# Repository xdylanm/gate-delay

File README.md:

# Gate Delay

A gate delay module in the Eurorack format. The module is implemented with an ATTiny13a microcontroller, with features including

* delays ranging from about 8ms to 2s
* gate pulse length is maintined
* sequences of up to 4 pulses can be delayed

A second, fully analog design is also described. This design is based on a current mirror and integration capacitor, and also maintains the gate pulse length. I have not implemented and tested this one.

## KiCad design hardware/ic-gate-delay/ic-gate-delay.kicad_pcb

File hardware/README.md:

The 'dual-gate-delay' project contains the hardware design for the v1.0 module. The 'gate-delay' project only contains schematic sketches (for reference related to the analog variant of the design). The 'ic-gate-delay' project is the v2.0 module (single gate delay with expanded IO).

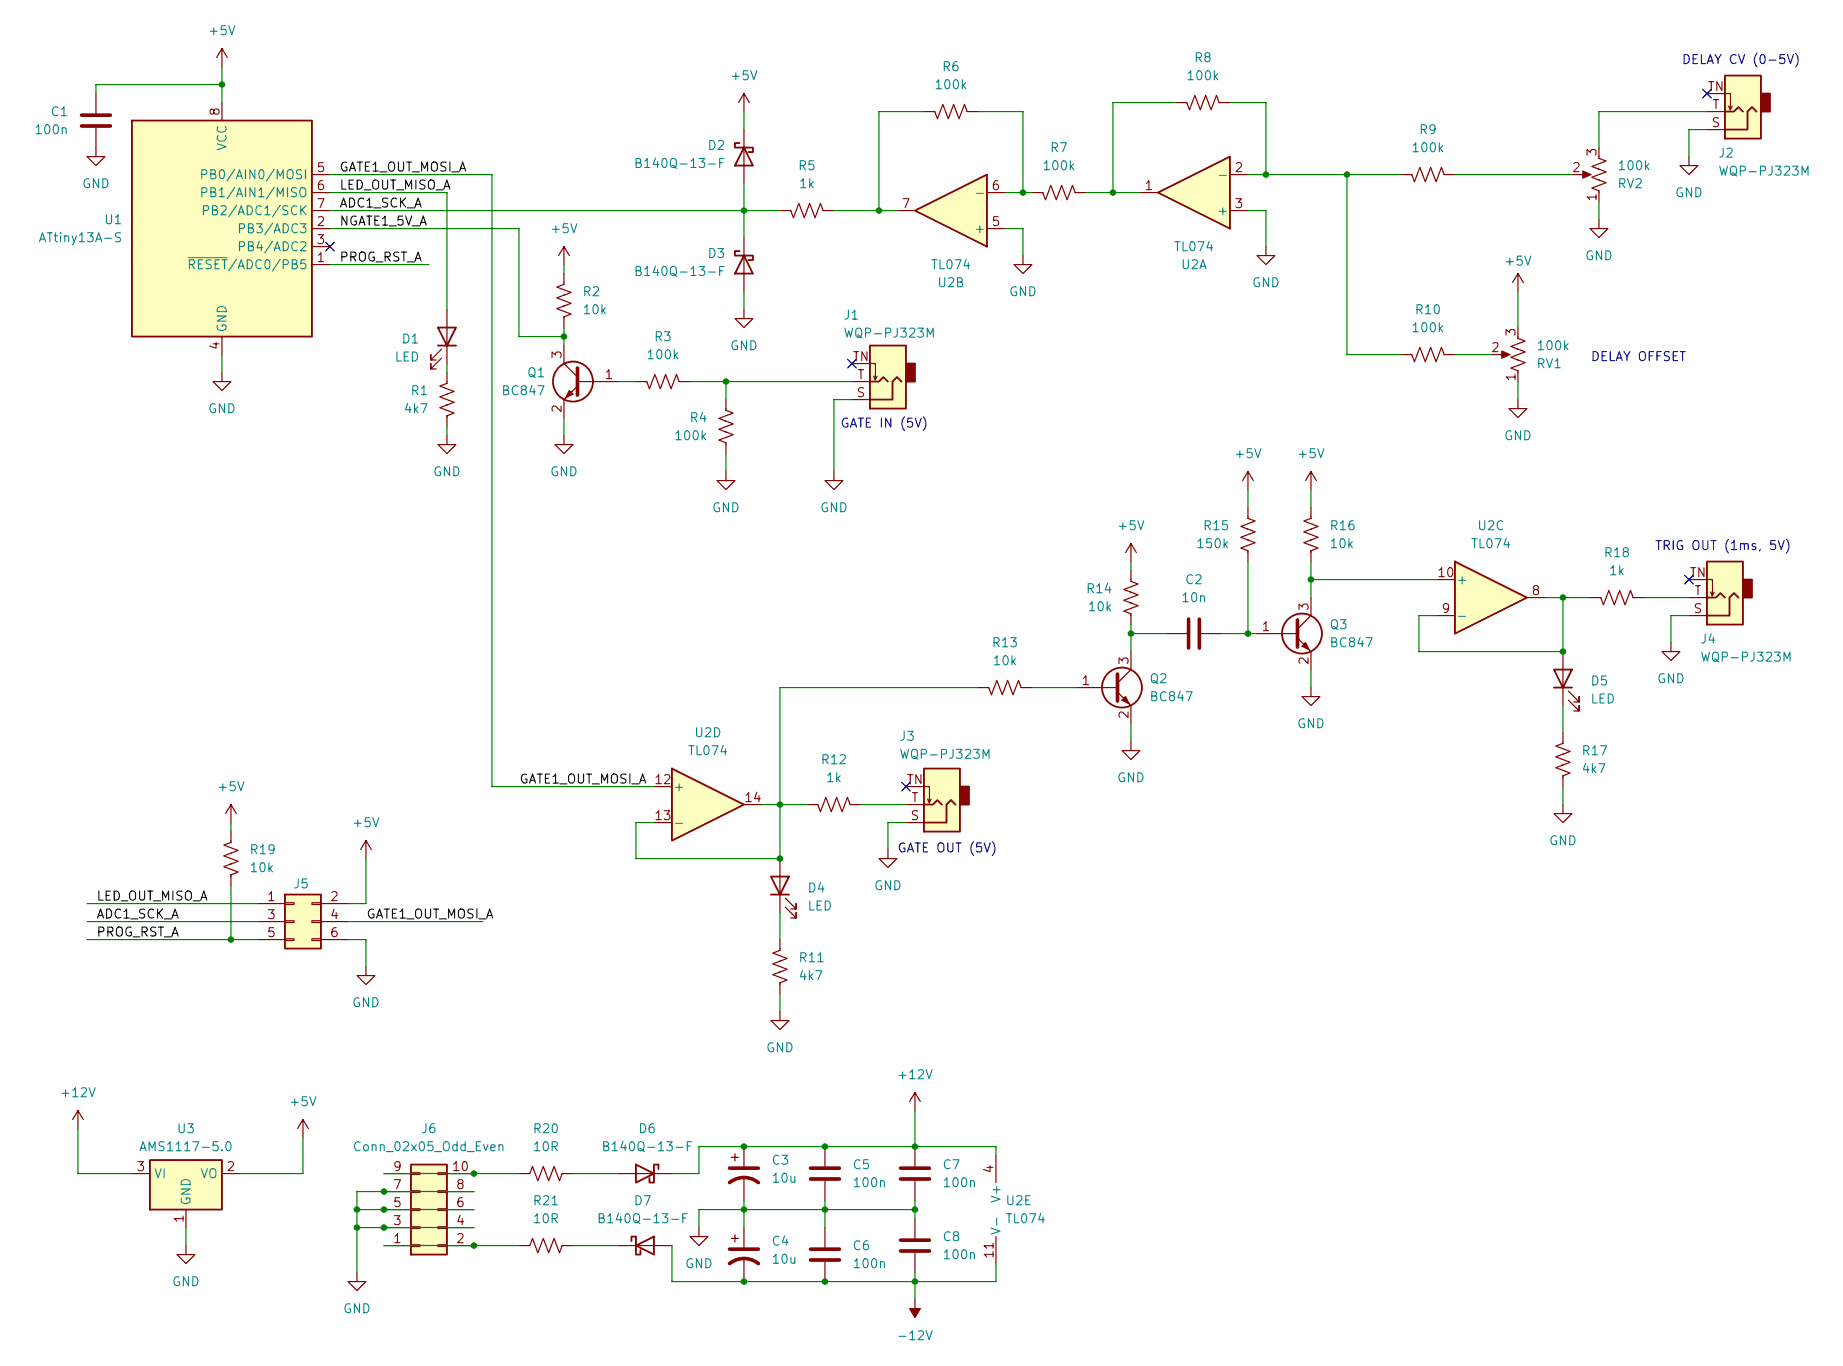
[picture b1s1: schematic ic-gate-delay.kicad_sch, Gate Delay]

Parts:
C1, C5, C6, C7, C8: 100n; C_0805_2012Metric
C2: 10n; C_0805_2012Metric
C3, C4: 10u; CP_Radial_D5.0mm_P2.50mm
D1: LED; LED_0805_2012Metric_Pad1.15x1.40mm_HandSolder
D2, D3, D6, D7: B140Q-13-F; D_SMA_Handsoldering
D4, D5: LED; LED_D3.0mm
J1, J2, J3, J4: WQP-PJ323M; Jack_3.5mm_QingPu_WQP-PJ323M_Horizontal
J5: Conn_02x03_Odd_Even; PinHeader_2x03_P2.54mm_Vertical
J6: Conn_02x05_Odd_Even; IDC-Header_2x05_P2.54mm_Horizontal
Q1, Q2, Q3: BC847; SOT-23
R1, R11, R17: 4k7; R_0805_2012Metric_Pad1.20x1.40mm_HandSolder
R2, R13, R14, R16, R19: 10k; R_0805_2012Metric_Pad1.20x1.40mm_HandSolder
R3, R4, R6, R7, R8, R9, R10: 100k; R_0805_2012Metric_Pad1.20x1.40mm_HandSolder
R5, R12, R18: 1k; R_0805_2012Metric_Pad1.20x1.40mm_HandSolder
R15: 150k; R_0805_2012Metric_Pad1.20x1.40mm_HandSolder
R20, R21: 10R; R_0805_2012Metric_Pad1.20x1.40mm_HandSolder
RV1, RV2: 100k; Potentiometer_Bourns_PTV09A-2_Single_Horizontal
U1: ATtiny13A-S; SOIC-8_3.9x4.9mm_P1.27mm
U2: TL074; SOIC-14_3.9x8.7mm_P1.27mm
U3: AMS1117-5.0; SOT-223-3_TabPin2

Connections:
+5V: C1.1, D2.1 (K), J5.2, R2.1, R14.1, R15.1, R16.1, R19.1, RV1.3, U1.8 (VCC), U3.2 (VO)
+12V: C3.1, C5.1, C7.1, D6.1 (K), U2.4 (V+), U3.3 (VI)
-12V: C4.2, C6.2, C8.2, D7.2 (A), U2.11 (V-)
/ADC1_SCK_A: D2.2 (A), D3.1 (K), J5.3, R5.1, U1.7 (PB2/ADC1/SCK)
/GATE1_OUT_MOSI_A: J5.4, U1.5 (PB0/AIN0/MOSI), U2.12 (+)
/LED_OUT_MISO_A: D1.2 (A), J5.1, U1.6 (PB1/AIN1/MISO)
/NGATE1_5V_A: Q1.3 (C), R2.2, U1.2 (PB3/ADC3)
/PROG_RST_A: J5.5, R19.2, U1.1 (~RESET/ADC0/PB5)
GND: C1.2, C3.2, C4.1, C5.2, C6.1, C7.2, C8.1, D3.2 (A), J1.S, J2.S, J3.S, J4.S, J5.6, J6.3, J6.4, J6.5, J6.6, J6.7, J6.8, Q1.2 (E), Q2.2 (E), Q3.2 (E), R1.2, R4.2, R11.2, R17.2, RV1.1, RV2.1, U1.4 (GND), U2.3 (+), U2.5 (+), U3.1 (GND)
unnamed: D1.1 (K), R1.1
unnamed: D4.2 (A), R12.2, R13.2, U2.13 (-), U2.14
unnamed: D4.1 (K), R11.1
unnamed: D5.2 (A), R18.2, U2.8, U2.9 (-)
unnamed: D5.1 (K), R17.1
unnamed: D6.2 (A), R20.2
unnamed: D7.1 (K), R21.2
unnamed: J1.T, R3.1, R4.1
unnamed: J2.T, RV2.3
unnamed: J3.T, R12.1
unnamed: J4.T, R18.1
unnamed: J6.1, J6.2, R21.1
unnamed: J6.9, J6.10, R20.1
unnamed: Q1.1 (B), R3.2
unnamed: Q2.1 (B), R13.1
unnamed: C2.1, Q2.3 (C), R14.2
unnamed: C2.2, Q3.1 (B), R15.2
unnamed: Q3.3 (C), R16.2, U2.10 (+)
unnamed: R5.2, R6.1, U2.7
unnamed: R7.2, R8.1, U2.1
unnamed: R9.2, RV2.2
unnamed: R10.2, RV1.2
unnamed: R8.2, R9.1, R10.1, U2.2 (-)
unnamed: R6.2, R7.1, U2.6 (-)

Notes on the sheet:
DELAY OFFSET
GATE IN (5V)
TRIG OUT (1ms, 5V)
GATE OUT (5V)
DELAY CV (0-5V)

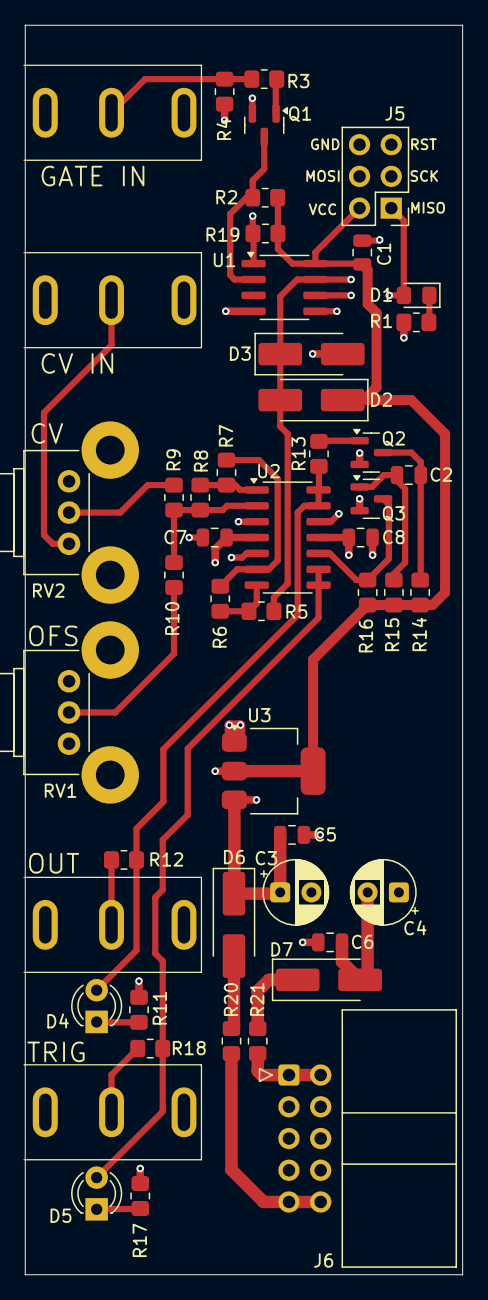
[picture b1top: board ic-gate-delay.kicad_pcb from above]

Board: 4 copper layers, 35.0 x 100.0 mm, 50 parts (0 on the bottom side), 33 nets.

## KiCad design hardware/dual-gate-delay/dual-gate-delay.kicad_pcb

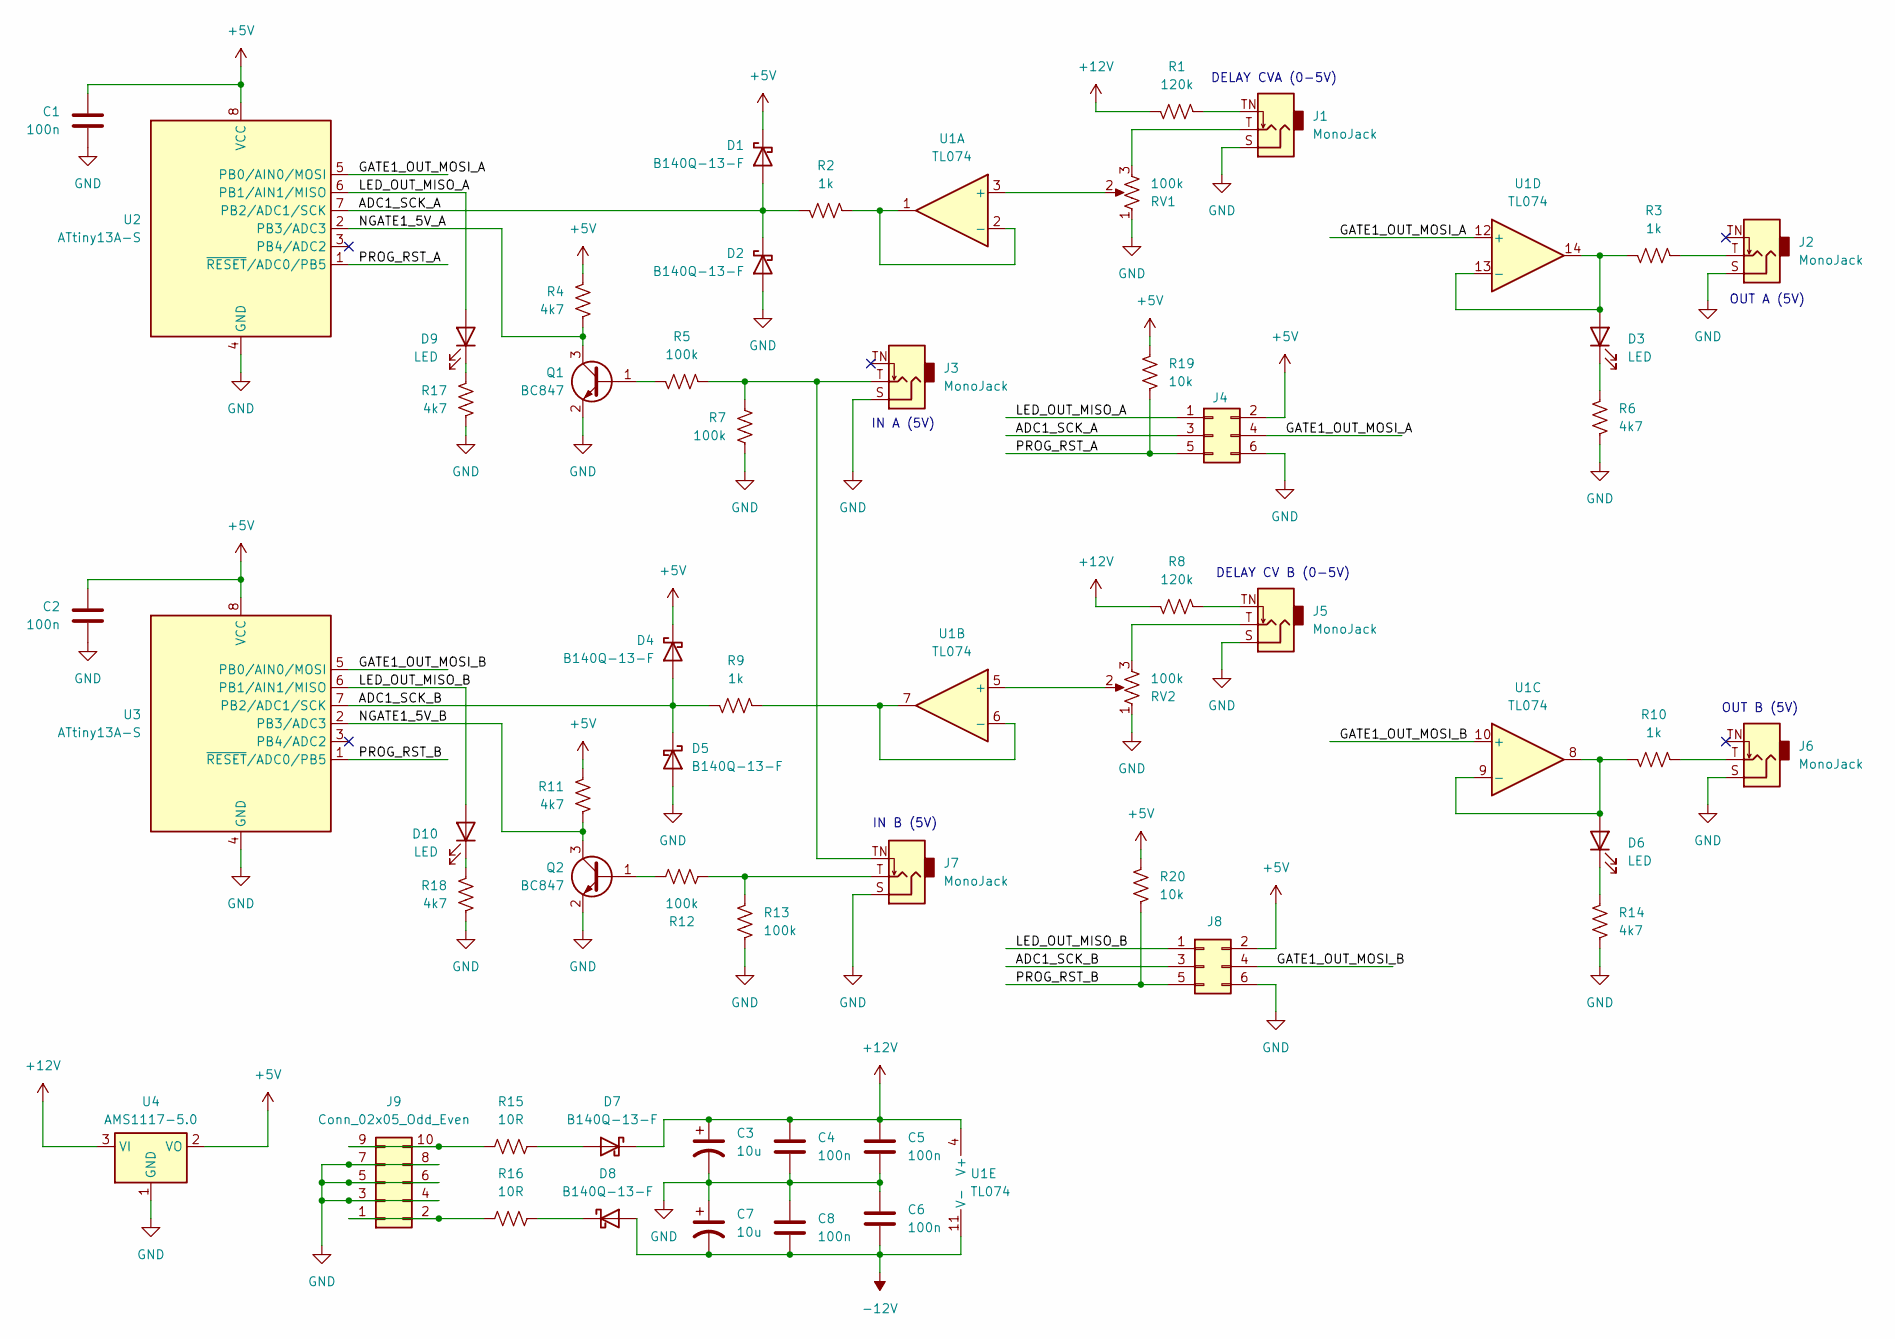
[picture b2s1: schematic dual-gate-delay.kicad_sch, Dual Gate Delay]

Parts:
C1, C2, C4, C5, C6, C8: 100n; C_0805_2012Metric
C3, C7: 10u; CP_Radial_D5.0mm_P2.50mm
D1, D2, D4, D5, D7, D8: B140Q-13-F; D_SMA_Handsoldering
D3, D6: LED; LED_D3.0mm
D9, D10: LED; LED_0805_2012Metric_Pad1.15x1.40mm_HandSolder
J1, J2, J3, J5, J6, J7: MonoJack; Jack_3.5mm_QingPu_WQP-PJ323M_Horizontal
J4, J8: Conn_02x03_Odd_Even; PinHeader_2x03_P2.54mm_Vertical
J9: Conn_02x05_Odd_Even; IDC-Header_2x05_P2.54mm_Horizontal
Q1, Q2: BC847; SOT-23
R1, R8: 120k; R_0805_2012Metric_Pad1.20x1.40mm_HandSolder
R2, R3, R9, R10: 1k; R_0805_2012Metric_Pad1.20x1.40mm_HandSolder
R4, R6, R11, R14, R17, R18: 4k7; R_0805_2012Metric_Pad1.20x1.40mm_HandSolder
R5, R7, R12, R13: 100k; R_0805_2012Metric_Pad1.20x1.40mm_HandSolder
R15, R16: 10R; R_0805_2012Metric_Pad1.20x1.40mm_HandSolder
R19, R20: 10k; R_0805_2012Metric_Pad1.20x1.40mm_HandSolder
RV1, RV2: 100k; Potentiometer_Bourns_PTV09A-2_Single_Horizontal
U1: TL074; SOIC-14_3.9x8.7mm_P1.27mm
U2, U3: ATtiny13A-S; SOIC-8_3.9x4.9mm_P1.27mm
U4: AMS1117-5.0; SOT-223-3_TabPin2

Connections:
+5V: C1.1, C2.1, D1.1 (K), D4.1 (K), J4.2, J8.2, R4.1, R11.1, R19.1, R20.1, U2.8 (VCC), U3.8 (VCC), U4.2 (VO)
+12V: C3.1, C4.1, C5.1, D7.1 (K), R1.1, R8.1, U1.4 (V+), U4.3 (VI)
-12V: C6.2, C7.2, C8.2, D8.2 (A), U1.11 (V-)
/ADC1_SCK_A: D1.2 (A), D2.1 (K), J4.3, R2.1, U2.7 (PB2/ADC1/SCK)
/ADC1_SCK_B: D4.2 (A), D5.1 (K), J8.3, R9.1, U3.7 (PB2/ADC1/SCK)
/GATE1_OUT_MOSI_A: J4.4, U1.12 (+), U2.5 (PB0/AIN0/MOSI)
/GATE1_OUT_MOSI_B: J8.4, U1.10 (+), U3.5 (PB0/AIN0/MOSI)
/LED_OUT_MISO_A: D9.2 (A), J4.1, U2.6 (PB1/AIN1/MISO)
/LED_OUT_MISO_B: D10.2 (A), J8.1, U3.6 (PB1/AIN1/MISO)
/NGATE1_5V_A: Q1.3 (C), R4.2, U2.2 (PB3/ADC3)
/NGATE1_5V_B: Q2.3 (C), R11.2, U3.2 (PB3/ADC3)
/PROG_RST_A: J4.5, R19.2, U2.1 (~RESET/ADC0/PB5)
/PROG_RST_B: J8.5, R20.2, U3.1 (~RESET/ADC0/PB5)
GND: C1.2, C2.2, C3.2, C4.2, C5.2, C6.1, C7.1, C8.1, D2.2 (A), D5.2 (A), J1.S, J2.S, J3.S, J4.6, J5.S, J6.S, J7.S, J8.6, J9.3, J9.4, J9.5, J9.6, J9.7, J9.8, Q1.2 (E), Q2.2 (E), R6.2, R7.2, R13.2, R14.2, R17.2, R18.2, RV1.1, RV2.1, U2.4 (GND), U3.4 (GND), U4.1 (GND)
unnamed: D3.2 (A), R3.2, U1.13 (-), U1.14
unnamed: D3.1 (K), R6.1
unnamed: D6.2 (A), R10.2, U1.8, U1.9 (-)
unnamed: D6.1 (K), R14.1
unnamed: D7.2 (A), R15.2
unnamed: D8.1 (K), R16.2
unnamed: D9.1 (K), R17.1
unnamed: D10.1 (K), R18.1
unnamed: J1.T, RV1.3
unnamed: J1.TN, R1.2
unnamed: J2.T, R3.1
unnamed: J3.T, J7.TN, R5.1, R7.1
unnamed: J5.T, RV2.3
unnamed: J5.TN, R8.2
unnamed: J6.T, R10.1
unnamed: J7.T, R12.1, R13.1
unnamed: J9.1, J9.2, R16.1
unnamed: J9.9, J9.10, R15.1
unnamed: Q1.1 (B), R5.2
unnamed: Q2.1 (B), R12.2
unnamed: RV1.2, U1.3 (+)
unnamed: R2.2, U1.1, U1.2 (-)
unnamed: RV2.2, U1.5 (+)
unnamed: R9.2, U1.6 (-), U1.7

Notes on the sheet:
DELAY CV B (0-5V)
IN A (5V)
OUT B (5V)
OUT A (5V)
DELAY CVA (0-5V)
IN B (5V)

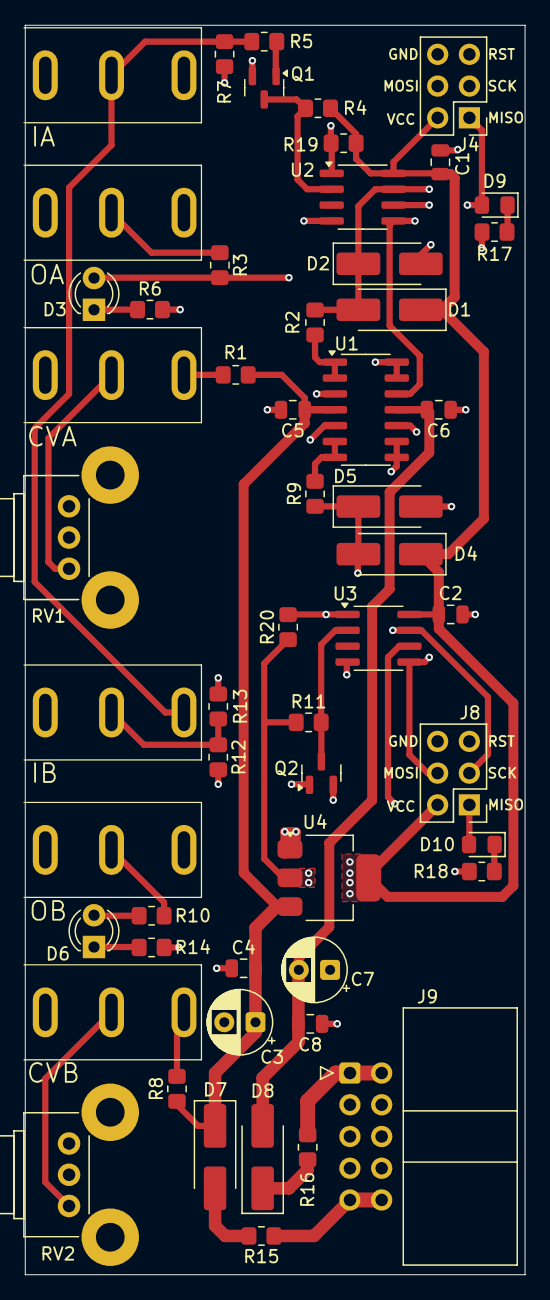
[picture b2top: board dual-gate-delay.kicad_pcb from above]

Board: 4 copper layers, 40.0 x 100.0 mm, 55 parts (0 on the bottom side), 38 nets.

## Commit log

2025-09-28 Initial commit to separate repository for this module (previously contained in the ADSR-EG module). Updated docs to build.
2025-10-16 plots
2025-10-16 Migrated to mkdocs/material & some documentation clean up. Added schematic and BOM
2025-10-16 Added module image
2025-11-05 Initial project for dual gate delay faceplate, small PBC revisions (SMT BJTs, moved LED)
2025-11-11 v2 PCB and faceplate with single gate delay circuit
2025-11-11 Updating readmes
2025-12-27 Updates with build from IC gate delay

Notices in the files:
hardware/dual-gate-delay/dual-gate-delay.kicad_pcb:
CC BY-SA 4.0
idyllm CC BY-SA 4.0
